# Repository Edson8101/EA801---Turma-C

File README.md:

# EA801

Este repositório apresenta os projetos desenvolvidos pelos estudantes da FEEC-UNICAMP na disciplina de graduação denominada Laboratório de Sistemas Embarcados.

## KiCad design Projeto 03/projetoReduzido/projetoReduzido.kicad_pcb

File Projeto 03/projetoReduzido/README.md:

# Projeto de sistema de audiometria portátil de baixo custo [Parte 3] - EA801/Projeto 3

**Autores:**
- **Henrique Stumm Rocha**
  - *Faculdade de Engenharia Elétrica e de Computação (FEEC), Universidade Estadual de Campinas*
  - *Email: h239694@dac.unicamp.br*
- **Vitor Rolim Cardoso**
  - *Faculdade de Engenharia Elétrica e de Computação (FEEC), Universidade Estadual de Campinas*
  - *Email: v204077@dac.unicamp.br*

---

## Introdução

A elevada complexidade e custo de equipamentos de audiometria tradicional (como o `\cite{formis2023}`, comercializado por R$15.990,00) limitam seu acesso em contextos de baixo orçamento, como clínicas de pequeno porte e regiões com recursos limitados. Sistemas embarcados, como os baseados em ESP32 ou Raspberry Pi, surgem como alternativas promissoras: com componentes de baixo custo, permitem implementar funcionalidades básicas de teste auditivo de forma portátil e acessível. No documento a seguir, apresentamos um sistema de audiometria básico utilizando o microcontrolador RP2350 `\cite{rp2350}` integrado à placa de desenvolvimento BitDogLab `\cite{bitdoglab}`, junto com uma série de componentes periféricos que permitem à placa de circuitos BitDogLab se comunicar com fones de ouvido analógicos P2.

Essa abordagem não substitui equipamentos profissionais, mas pode viabilizar triagens preliminares em condições em que o acesso a equipamentos tradicionais representa um custo proibitivo.

## Descrição Funcional

### Objetivo

O programa é um sistema interativo para avaliação auditiva em formato de jogo, onde o usuário deve identificar e responder a tons de frequências variadas emitidos por dois buzzers. O sistema fornece feedback visual imediato (via LED RGB) e histórico (via matriz de LEDs) sobre a precisão das respostas, simulando um teste de audiometria simplificado. Nessa terceira etapa do projeto, integramos todo o desenvolvimento do hardware em uma placa de circuito impresso (PCB) capaz de realizar a conexão entre todos os componentes e a conversão do sinal diferencial do amplificador classe D para sinal single-ended.

### Componentes Principais

* **Botões (2 unidades):**
    * O usuário deve pressionar o botão correspondente ao buzzer que emitiu o tom durante sua execução.
    * Respostas fora do intervalo do tom ou pressionamento do botão errado são consideradas incorretas.
* **Matriz de LEDs NeoPixel (5x5):**
    * Exibe um histórico sequencial das respostas:
        * Verde: Resposta correta (botão pressionado durante o tom).
        * Vermelho: Resposta ausente, incorreta ou fora do tempo.
    * Os LEDs são preenchidos da direita para a esquerda e de baixo para cima, reiniciando após 25 respostas.
* **LED RGB:**
    * Fornece feedback temporário (1 segundo) após cada resposta:
        * Verde: Resposta incorreta.
        * Vermelho: Resposta correta.
        * Magenta: Resposta ausente ou fora do tempo.
* **PCM5102:**
    * Conversor Digital-Analógico:
        * Recebe um sinal digital em protocolo I2S da BitDogLab e o converte em um sinal analógico de 2.1V centrado no GND.
        * Datasheet `\cite{PCM5102}`.
* **PAM8403:**
    * Amplificador de Áudio:
        * Recebe um sinal analógico do Conversor D/A PCM5102 e o amplifica para 5V de saída.
        * É um amplificador sem filtro, portanto, é necessário colocar um filtro LC na saída para atenuar o ruído no alto-falante.
        * Datasheet `\cite{PAM8403}`.
* **Filtro LC:**
    * Conjunto de indutores e capacitores para atenuar o ruído da saída do amplificador:
        * Para cada saída P2 temos um indutor de 10 uH e um capacitor de 470 nF conectados em série.
        * Foi necessário usar o filtro LC para filtrar o sinal PWM, que é característico de amplificador tipo D.
* **Saída de Áudio:**
    * A saída de áudio do projeto, agora integrada em uma PCB, é composta pelos seguintes elementos:
        * **Circuito de Conversão (LM324):** O sinal de áudio, gerado internamente de forma diferencial, é processado por um amplificador operacional **LM324**. Ele está configurado como um amplificador diferencial com ganho de atenuação (0.082) para converter o sinal para o formato single-ended e, ao mesmo tempo, eliminar o estouramento (clipping) do áudio.
        * **Conector de Saída P2:** O sinal já convertido é disponibilizado em um conector de áudio padrão P2 (3.5mm), permitindo a conexão universal com a maioria dos dispositivos de áudio.
        * **Carga de Saída (Fone de Ouvido):** O circuito foi projetado e validado para alimentar a carga de saída, especificamente um fone de 38.5 ohms (operando a 0.41 V), garantindo que o LM324 forneça o sinal com qualidade e sem perdas, mesmo considerando sua baixa capacidade de fornecer corrente para o fone.

### Funcionamento do Sistema

#### 1. Geração de Tons Aleatórios
* **Frequências:** Selecionadas aleatoriamente da lista `FREQUENCIAS_AUDIOMETRIA` (125 Hz a 8000 Hz).
* **Volume:** Amplitude aleatória (128 a 2048) para simular variações de intensidade sonora.
* **Buzzer Ativo:** Escolhido aleatoriamente (Buzzer 1 ou 2) a cada rodada.

#### 2. Lógica de Resposta
* **Tempo de Resposta:** O usuário tem 1 segundo para pressionar o botão correto após o início do tom.
* **Validação:**
    * Acerto: Botão correto pressionado durante o tom → LED RGB vermelho + LED verde na matriz.
    * Erro:
        * Botão errado pressionado → LED RGB verde + LED vermelho na matriz.
        * Nenhum botão pressionado → LED RGB magenta + LED vermelho na matriz.

#### 3. Matriz de LEDs (NeoPixel)
* **Sequenciamento:** Cada resposta acende um LED na posição atual (`current_led_index`), avançando até o 25º LED.
* **Reinício:** Ao chegar ao 25º LED, a matriz é apagada e o sequenciamento recomeça.
* **Brilho:** Configurado em nível reduzido (`BRILHO = 10`) para evitar saturação visual.

#### 4. LED RGB
* **Controle:**
    * Verde: `set_led_color(0, 1, 0)` (resposta incorreta).
    * Vermelho: `set_led_color(1, 0, 0)` (resposta correta).
    * Magenta: `set_led_color(0, 0, 1)` (resposta fora do tempo).
    * Desligado: Após 1 segundo, independentemente do resultado.

#### 5. Temporização e Aleatoriedade
* **Intervalo entre Tons:** 2 a 5 segundos (aleatório) para evitar padrões previsíveis.
* **Duração do Tom:** 1 segundo por padrão.

### Fluxo de Operação
1.  **Inicialização:**
    * LEDs RGB e matriz são desligados.
2.  **Loop Principal:**
    * Aguarda um intervalo aleatório (2-5 segundos).
    * Seleciona buzzer, frequência e volume aleatoriamente.
    * Toca o tom no buzzer escolhido.
    * Monitora pressionamento do botão correspondente durante o tom.
    * Atualiza a matriz de LEDs e o LED RGB conforme a resposta.
    * Repete o processo indefinidamente.

### Casos de Uso
* Teste Auditivo: Avaliação da capacidade do usuário de identificar tons em diferentes frequências e volumes.
* Treino de Discriminação Sonora: Prática para distinguir sons entre dois pontos (fones esquerdo/direito).
* Demonstração Visual: A matriz de LEDs serve como placar dinâmico para acompanhamento de progresso.

### Notas Técnicas
* **Microcontrolador:** Raspberry Pi Pico (RP2040) com suporte a PIO para geração de clock dedicado.
* **Clock de Alta Precisão:**
    * Gerador de clock de 1.024MHz via PIO (GP16).
    * Configuração PLL para sincronismo com PCM5102.
* **Conexões Principais:**
    * Interface I2S para PCM5102:
        * BCK: GP18 (Bit Clock)
        * LRCK: GP19 (Word Select)
        * DIN: GP20 (Dados de Áudio)
    * Controles:
        * Botões: GP5 (Canal Esquerdo), GP6 (Canal Direito)
        * Matriz NeoPixel: GP7 (25 LEDs, brilho configurável)
        * LED RGB: GP11 (Azul), GP12 (Vermelho), GP13 (Verde)
* **Parâmetros Customizáveis:**
    * Audio:
        * Taxa de amostragem (16kHz padrão)
        * Buffer I2S (1024 bytes)
        * Faixas de frequência (125Hz-8kHz)
    * Visuais:
        * Brilho LEDs (0-255)
        * Padrões de matriz (histórico de 25 testes)
        * Cores de feedback RGB
    * Lógica:
        * Intervalos entre testes (2-5s)
        * Níveis de amplitude (128-2048)
        * 
A equação abaixo descreve o comportamento da saída $V_o$ do amplificador diferencial, em função da entrada inversora $V_-$ e a entrada não inversora $V_+$. Os resistores estão rotulados como no esquemático.

$$
V_{o}=-\frac{R_{2}}{R_{1}}V_{-}+\frac{R_{4}}{R_{3}+R_{4}}\cdot\frac{R_{1}+R_{2}}{R_{1}} \cdot V_{+}
$$

###
Código de software do projeto disponível no arquivo .py dentro do diretório projetoReduzido. Esquemático da PCB e do circuito disponíveis no projeto kicad com a extensão .kicad_pro

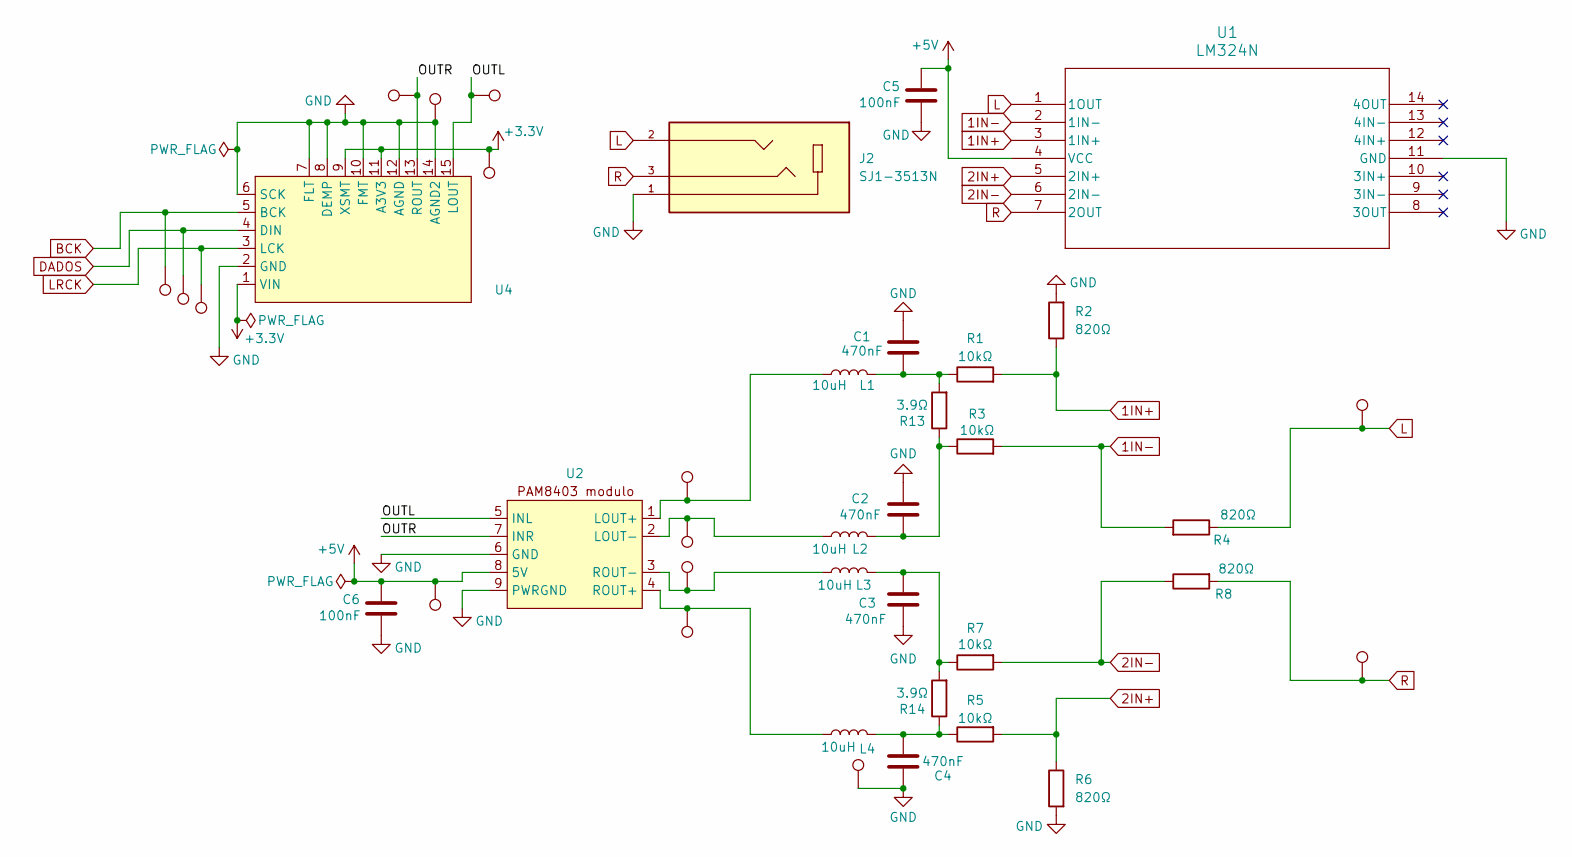
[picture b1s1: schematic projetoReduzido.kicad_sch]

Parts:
3V3, 5V0: TestPoint; TestPoint_THTPad_D4.0mm_Drill2.0mm
BCK2: TestPoint; TestPoint_THTPad_D4.0mm_Drill2.0mm
C1, C2, C3, C4: 470nF; CP_Axial_L10.0mm_D6.0mm_P15.00mm_Horizontal
C5, C6: 100nF; CP_Axial_L10.0mm_D6.0mm_P15.00mm_Horizontal
DADOS2: TestPoint; TestPoint_THTPad_D4.0mm_Drill2.0mm
GND1, GND3: TestPoint; TestPoint_THTPad_D4.0mm_Drill2.0mm
J2: SJ1-3513N; CUI_SJ1-3513N; PARTREV 1.02
L1, L2, L3, L4: 10uH; L_Axial_L5.3mm_D2.2mm_P10.16mm_Horizontal_Vishay_IM-1
LOUT+1: TestPoint; TestPoint_THTPad_D4.0mm_Drill2.0mm
LOUT-1: TestPoint; TestPoint_THTPad_D4.0mm_Drill2.0mm
LRCK2: TestPoint; TestPoint_THTPad_D4.0mm_Drill2.0mm
Left1: TestPoint; TestPoint_THTPad_D4.0mm_Drill2.0mm
OUTL1: TestPoint; TestPoint_THTPad_D4.0mm_Drill2.0mm
OUTR1: TestPoint; TestPoint_THTPad_D4.0mm_Drill2.0mm
R1, R3, R5, R7: 10kΩ; R_Axial_DIN0207_L6.3mm_D2.5mm_P10.16mm_Horizontal
R2, R4, R6, R8: 820Ω; R_Axial_DIN0207_L6.3mm_D2.5mm_P10.16mm_Horizontal
R13, R14: 3.9Ω; R_Axial_DIN0207_L6.3mm_D2.5mm_P10.16mm_Horizontal
ROUT+1: TestPoint; TestPoint_THTPad_D4.0mm_Drill2.0mm
ROUT-1: TestPoint; TestPoint_THTPad_D4.0mm_Drill2.0mm
Right1: TestPoint; TestPoint_THTPad_D4.0mm_Drill2.0mm
U1: LM324N; N14
U2: moduloPAM8403
U4: moduloPCM5102

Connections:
1IN+: R1.2, R2.1, U1.3 (1IN+)
1IN-: R3.2, R4.2, U1.2 (1IN-)
2IN+: R5.2, R6.1, U1.5 (2IN+)
2IN-: R7.2, R8.1, U1.6 (2IN-)
+3.3V: 3V3.1, U4.1 (VIN), U4.9 (XSMT), U4.11 (A3V3)
+5V: 5V0.1, C5.1, C6.1, U1.4 (VCC), U2.8 (5V)
/OUTL: OUTL1.1, U2.5 (INL), U4.15 (LOUT)
/OUTR: OUTR1.1, U2.7 (INR), U4.13 (ROUT)
BCK: BCK2.1, U4.5 (BCK)
DADOS: DADOS2.1, U4.4 (DIN)
GND: C1.2, C2.2, C3.1, C4.1, C5.2, C6.2, GND1.1, GND3.1, J2.1, R2.2, R6.2, U1.11 (GND), U2.6 (GND), U2.9 (PWRGND), U4.2 (GND), U4.6 (SCK), U4.7 (FLT), U4.8 (DEMP), U4.10 (FMT), U4.12 (AGND), U4.14 (AGND2)
L: J2.2, Left1.1, R4.1, U1.1 (1OUT)
LRCK: LRCK2.1, U4.3 (LCK)
unnamed: C1.1, L1.1, R1.1, R13.2
unnamed: C2.1, L2.1, R3.1, R13.1
unnamed: C3.2, L3.1, R7.1, R14.2
unnamed: C4.2, L4.1, R5.1, R14.1
unnamed: L1.2, LOUT+1.1, U2.1 (LOUT+)
unnamed: L2.2, LOUT-1.1, U2.2 (LOUT-)
unnamed: L4.2, ROUT+1.1, U2.4 (ROUT+)
unnamed: L3.2, ROUT-1.1, U2.3 (ROUT-)
R: J2.3, R8.2, Right1.1, U1.7 (2OUT)

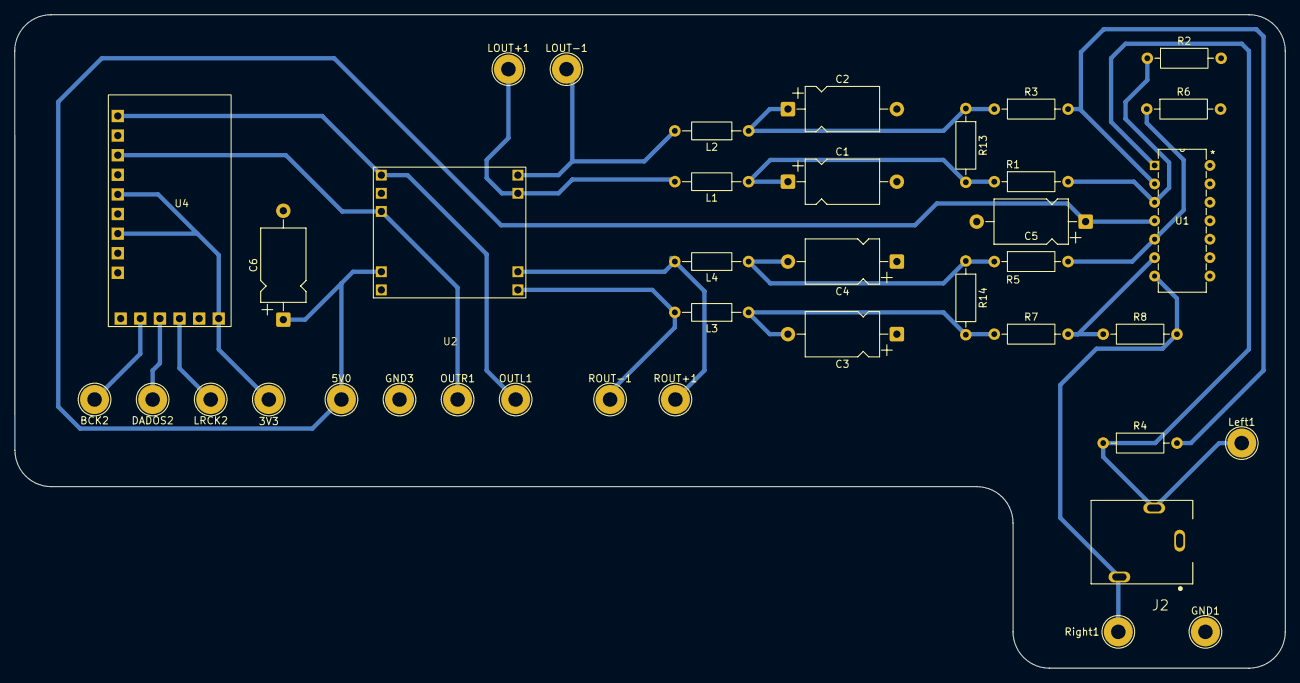
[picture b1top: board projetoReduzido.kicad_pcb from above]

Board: 2 copper layers, 175.0 x 90.0 mm, 39 parts (0 on the bottom side), 22 nets.

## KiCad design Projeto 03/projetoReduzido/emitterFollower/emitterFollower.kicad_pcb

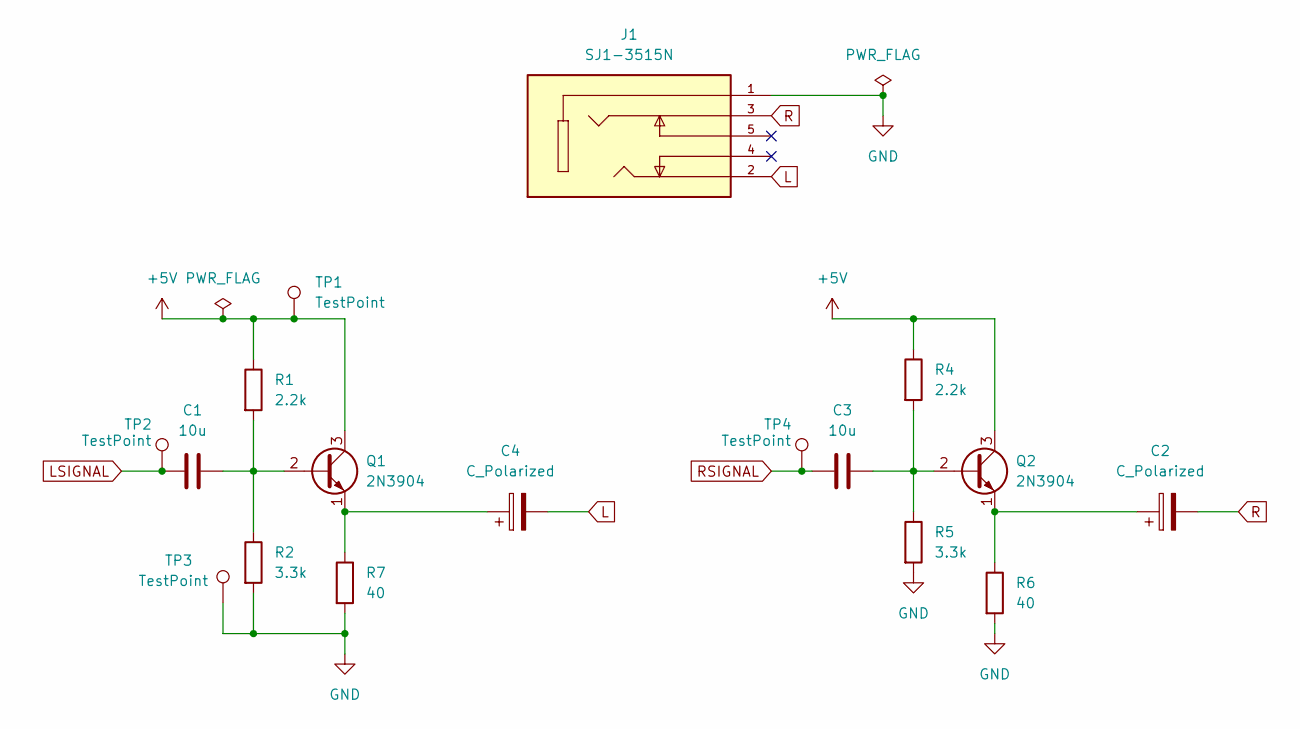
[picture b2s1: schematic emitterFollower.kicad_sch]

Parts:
C1, C3: 10u; CP_Radial_D5.0mm_P2.00mm; LCSC Part # C2960200
C2, C4: C_Polarized; CP_Radial_D10.0mm_P5.00mm; LCSC Part # C2960261
J1: SJ1-3515N; CUI_SJ1-3515N; PARTREV 1.03
Q1, Q2: 2N3904; TO-92_Inline
R1, R4: 2.2k; R_Axial_DIN0207_L6.3mm_D2.5mm_P10.16mm_Horizontal; LCSC Part # C58624
R2, R5: 3.3k; R_Axial_DIN0207_L6.3mm_D2.5mm_P10.16mm_Horizontal; LCSC Part # C58624
R6: 40; R_Axial_DIN0207_L6.3mm_D2.5mm_P10.16mm_Horizontal; LCSC C3352033
R7: 40; R_Axial_DIN0207_L6.3mm_D2.5mm_P10.16mm_Horizontal; LCSC Part # C3352033
TP1, TP2, TP3, TP4: TestPoint; TestPoint_THTPad_D4.0mm_Drill2.0mm

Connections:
+5V: Q1.3 (C), Q2.3 (C), R1.1, R4.1, TP1.1
GND: J1.1, R2.2, R5.2, R6.2, R7.2, TP3.1
L: C4.2, J1.2
LSIGNAL: C1.1, TP2.1
unnamed: C1.2, Q1.2 (B), R1.2, R2.1
unnamed: C4.1, Q1.1 (E), R7.1
unnamed: C3.2, Q2.2 (B), R4.2, R5.1
unnamed: C2.1, Q2.1 (E), R6.1
R: C2.2, J1.3
RSIGNAL: C3.1, TP4.1

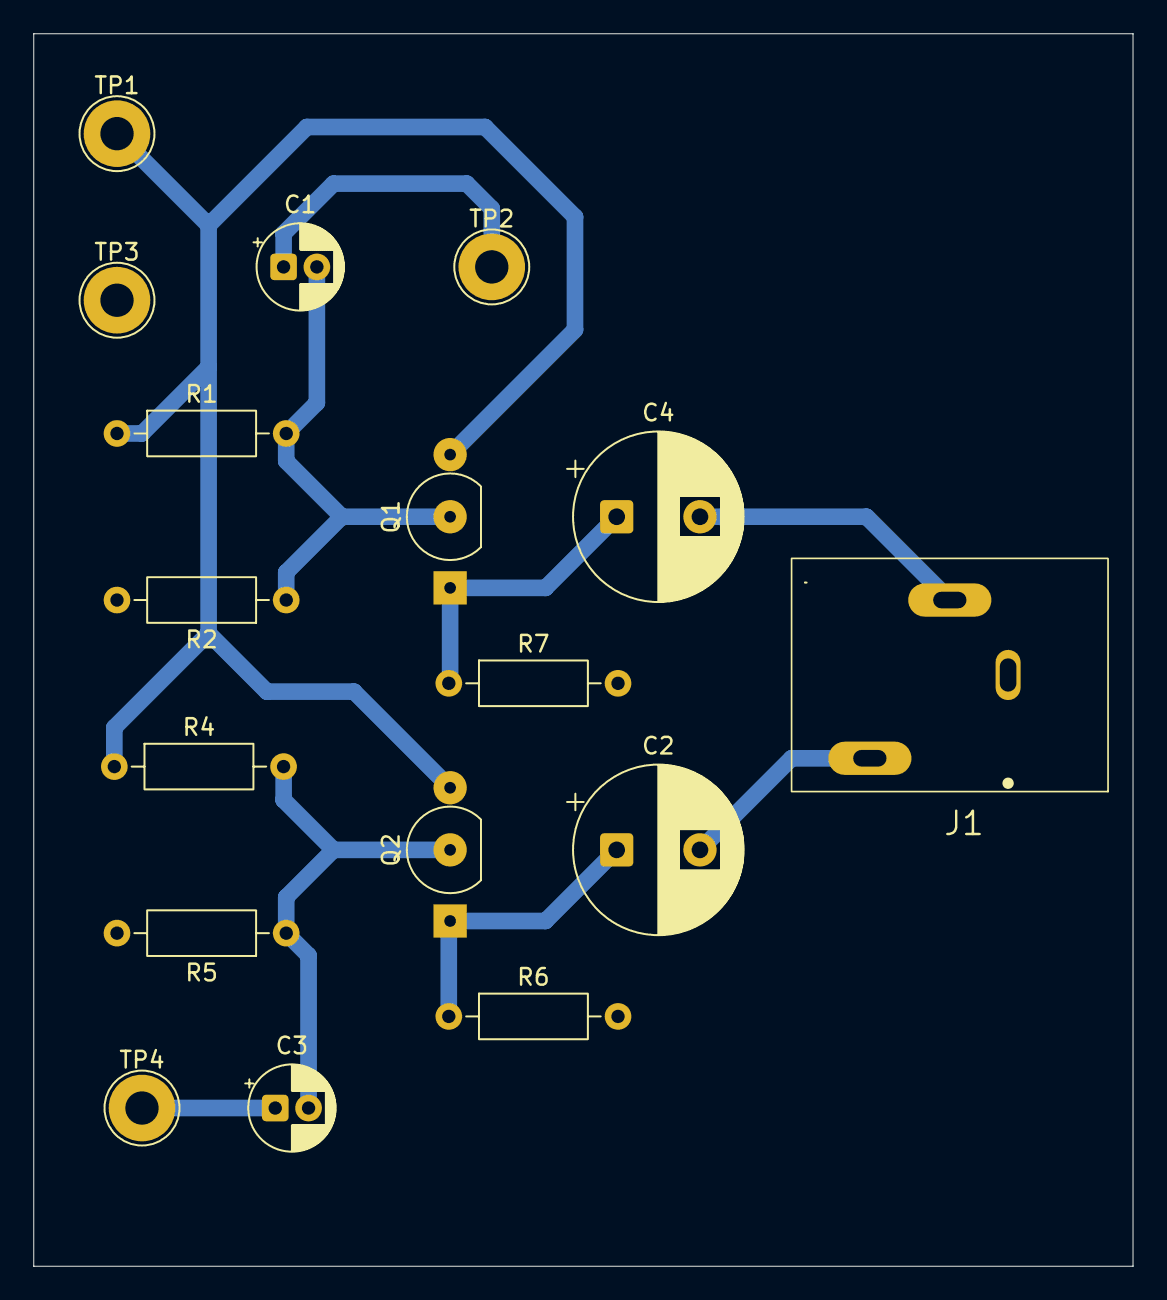
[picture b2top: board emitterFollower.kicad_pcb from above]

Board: 2 copper layers, 66.0 x 74.0 mm, 17 parts (0 on the bottom side), 10 nets.

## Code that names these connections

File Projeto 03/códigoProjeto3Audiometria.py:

"""
Programa de audiometria que utiliza o DAC PCM5102 para gerar tons puros
em diferentes frequencias, com saida estereo (canais esquerdo e direito separados)
e interface de botoes para resposta do paciente.
Autores: Vitor Rolim Cardoso (v204077@dac.unicamp.br) e Henrique Stumm Rocha (h239694@dac.unicamp.br)
"""

import machine
import rp2
from machine import Pin, I2S
import time
import random
import math
from neopixel import NeoPixel

############################################################
# Configuracao do Clock de 1.024MHz para o PCM5102
############################################################

@rp2.asm_pio(set_init=rp2.PIO.OUT_LOW)
def clock_gen():
    """Gera um sinal de clock de 1.024MHz usando PIO"""
    wrap_target()
    set(pins, 1) [1]  # Mantem nivel alto por 1 ciclo
    set(pins, 0) [1]  # Mantem nivel baixo por 1 ciclo
    wrap()

# Inicializa o clock no pino GP16
# Frequencia calculada para 16kHz de sample rate com PLL interno:
# BCK = 64 * Fs = 64 * 16000 = 1.024MHz
clock_pin = machine.Pin(16)
clock_sm = rp2.StateMachine(0, clock_gen, freq=1_024_000, set_base=clock_pin)
clock_sm.active(1)  # Ativa o clock

############################################################
# Configuracoes Globais do Audiometro
############################################################

# Frequencias padrao para teste auditivo (em Hz)
FREQUENCIAS_AUDIOMETRIA = [125, 250, 500, 1000, 2000, 4000, 8000]

# Configuracoes da matriz de LEDs
NUM_LEDS = 25        # Numero de LEDs na matriz
LED_PIN = 7          # Pino de controle da matriz
BRILHO = 20          # Intensidade dos LEDs (0-255)

# Taxa de amostragem do audio (Hz)
SAMPLE_RATE = 16000  # 16kHz, suficiente para frequencias ate 8kHz

############################################################
# Inicializacao de Hardware
############################################################

# Matriz de LEDs NeoPixel (feedback visual)
np = NeoPixel(Pin(LED_PIN), NUM_LEDS)
current_led_index = 0  # Indice do LED atual

# Botoes de resposta do paciente
botao1 = Pin(5, Pin.IN, Pin.PULL_UP)  # Botao para canal esquerdo
botao2 = Pin(6, Pin.IN, Pin.PULL_UP)  # Botao para canal direito

# LED RGB para feedback adicional
led_red = Pin(12, Pin.OUT)    # LED Vermelho
led_green = Pin(13, Pin.OUT)  # LED Verde
led_blue = Pin(11, Pin.OUT)   # LED Azul

############################################################
# Configuracao da Interface I2S para o PCM5102
############################################################

"""
Pinos I2S:
- BCK (Bit Clock): GP18 - Clock de bits (gerado automaticamente)
- LRCK (Word Select): GP19 - Selecao de canal (L/R)
- DIN (Data In): GP20 - Dados de audio

Configuracao do PCM5102:
- SCK aterrado: usa PLL interno
- BCK de 1.024MHz para 16kHz de sample rate
- Formato I2S padrao, 16 bits, estereo
"""
i2s = I2S(
    0,                      # ID do periferico I2S
    sck=Pin(18),            # BCK - Clock de bits
    ws=Pin(19),             # LRCK - Clock de palavras (Left/Right)
    sd=Pin(20),             # DIN - Dados de audio
    mode=I2S.TX,            # Modo transmissap
    bits=16,                # Resolucao de 16 bits
    format=I2S.STEREO,      # Formato estereo
    rate=SAMPLE_RATE,       # Taxa de amostragem
    ibuf=1024               # Tamanho do buffer interno
)

############################################################
# Funcoes Principais
############################################################

def generate_tone_chunk(freq, amplitude, phase, chunk_size, canal):
    """
    Gera um bloco de amostras de audio para um tom senoidal
    Args:
        freq: frequencia do tom em Hz
        amplitude: volume do som (0-32767)
        phase: fase atual do sinal
        chunk_size: numero de amostras a gerar
        canal: 0=esquerdo, 1=direito
    Returns:
        (samples, new_phase): tupla com amostras e nova fase
    """
    samples = bytearray(chunk_size * 4)  # 2 canais x 2 bytes por amostra
    volume = min(amplitude, 32767)      # Limita amplitude maxima
    
    for i in range(chunk_size):
        # Gera valor senoidal para o tom
        value = int(volume * math.sin(2 * math.pi * freq * (phase + i) / SAMPLE_RATE))
        
        if canal == 0:  # Canal esquerdo
            # Preenche canal esquerdo (little endian)
            samples[i*4] = value & 0xff       # Byte menos significativo
            samples[i*4+1] = (value >> 8) & 0xff  # Byte mais significativo
            # Canal direito em silencio
            samples[i*4+2] = 0
            samples[i*4+3] = 0
        else:  # Canal direito
            # Canal esquerdo em silencio
            samples[i*4] = 0
            samples[i*4+1] = 0
            # Preenche canal direito
            samples[i*4+2] = value & 0xff
            samples[i*4+3] = (value >> 8) & 0xff
    
    return samples, (phase + chunk_size) % SAMPLE_RATE

def update_led_matrix(correct):
    """
    Atualiza a matriz de LEDs com o historico de respostas
    Args:
        correct: True para resposta correta, False para incorreta
    """
    global current_led_index
    
    # Reinicia a matriz quando chega ao final
    if current_led_index >= NUM_LEDS:
        np.fill((0, 0, 0))
        np.write()
        current_led_index = 0
    
    # Define cor conforme acerto (verde) ou erro (vermelho)
    color = (0, BRILHO, 0) if correct else (BRILHO, 0, 0)
    np[current_led_index] = color
    np.write()
    current_led_index += 1

def set_led_color(red, green, blue):
    """
    Controla o LED RGB principal
    Args:
        red: estado do LED vermelho (0 ou 1)
        green: estado do LED verde (0 ou 1)
        blue: estado do LED azul (0 ou 1)
    """
    led_red.value(red)
    led_green.value(green)
    led_blue.value(blue)

def play_tone(freq, duration, correct_button, amplitude, canal):
    """
    Reproduz um tom pelo I2S e aguarda resposta do paciente
    Args:
        freq: frequencia do tom em Hz
        duration: duracao em segundos
        correct_button: botao correto para esta resposta
        amplitude: volume do som (0-32767)
        canal: 0=esquerdo, 1=direito
    """
    phase = 0  # Fase inicial do sinal
    start_time = time.ticks_ms()
    button_pressed = False
    correct_response = False
    chunk_size = 256  # Tamanho do bloco de amostras
    
    # Loop de reproducao do tom
    while time.ticks_diff(time.ticks_ms(), start_time) < duration * 1000:
        # Gera e envia bloco de amostras
        chunk, phase = generate_tone_chunk(freq, amplitude, phase, chunk_size, canal)
        i2s.write(chunk)
        
        # Verifica botoes
        if correct_button.value() == 0:  # Botao correto pressionado
            button_pressed = True
            correct_response = True
        elif ((canal == 0 and botao2.value() == 0) or 
              (canal == 1 and botao1.value() == 0)):
            button_pressed = True
            correct_response = False
    
    # Finaliza reproducao
    i2s.deinit()
    
    # Feedback visual
    if button_pressed:
        update_led_matrix(correct_response)
        set_led_color(0, 1 if correct_response else 0, 0 if correct_response else 1)
    else:
        update_led_matrix(False)  # Nenhuma resposta
        set_led_color(1, 1, 0)   # Amarelo para timeout
    
    time.sleep(1)  # Pausa entre tons
    set_led_color(0, 0, 0)  # Desliga LED RGB

############################################################
# Loop Principal
############################################################

def main():
    """Funcao principal do programa"""
    # Inicializa hardware
    clock_sm.active(1)  # Garante clock ativo
    set_led_color(0, 0, 0)  # LED RGB desligado
    np.fill((0, 0, 0))  # Matriz de LEDs apagada
    np.write()
    
    # Loop infinito de teste auditivo
    while True:
        # Seleciona canal aleatorio (0=esquerdo, 1=direito)
        canal = random.choice([0, 1])
        botao_correto = botao1 if canal == 0 else botao2
        
        # Intervalo aleatorio entre tons (2-5 segundos)
        time.sleep(random.uniform(2, 5))
        
        # Configura parametros do tom
        nivel_sinal = random.randint(128, 2048)  # Amplitude aleatoria
        tom_freq = random.choice(FREQUENCIAS_AUDIOMETRIA)  # Frequencia padrao
        
        # Reconfigura interface I2S para garantir sincronismo
        global i2s
        i2s = I2S(
            0,
            sck=Pin(18),
            ws=Pin(19),
            sd=Pin(20),
            mode=I2S.TX,
            bits=16,
            format=I2S.STEREO,
            rate=SAMPLE_RATE,
            ibuf=1024
        )
        
        # Reproduz o tom e aguarda resposta
        play_tone(tom_freq, 1, botao_correto, nivel_sinal, canal)

# Ponto de entrada do programa
if __name__ == "__main__":
    main()

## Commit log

2025-04-07 Codigos em micropython do projeto
2025-04-07 Pesos e Biases do modelo mnist pre-treinado
2025-04-07 Create teste
2025-04-07 Exemplos de imagens no formato adequado para testes no microcontrolador
2025-05-13 Create BitDog_Pet
2025-05-13 FuncoesControleRobo
2025-05-13 mudancas
2025-06-28 Create projetoReduzido.md
    markdown do projeto
2025-06-28 Rename projetoReduzido(1).md to README.md
2025-06-29 CodigoCachorro
2025-06-29 ConfiguraHC05
2025-06-29 ControleDoCachorro
2025-07-16 Create descricao
2025-07-16 descricao
2025-07-16 descricao.md
